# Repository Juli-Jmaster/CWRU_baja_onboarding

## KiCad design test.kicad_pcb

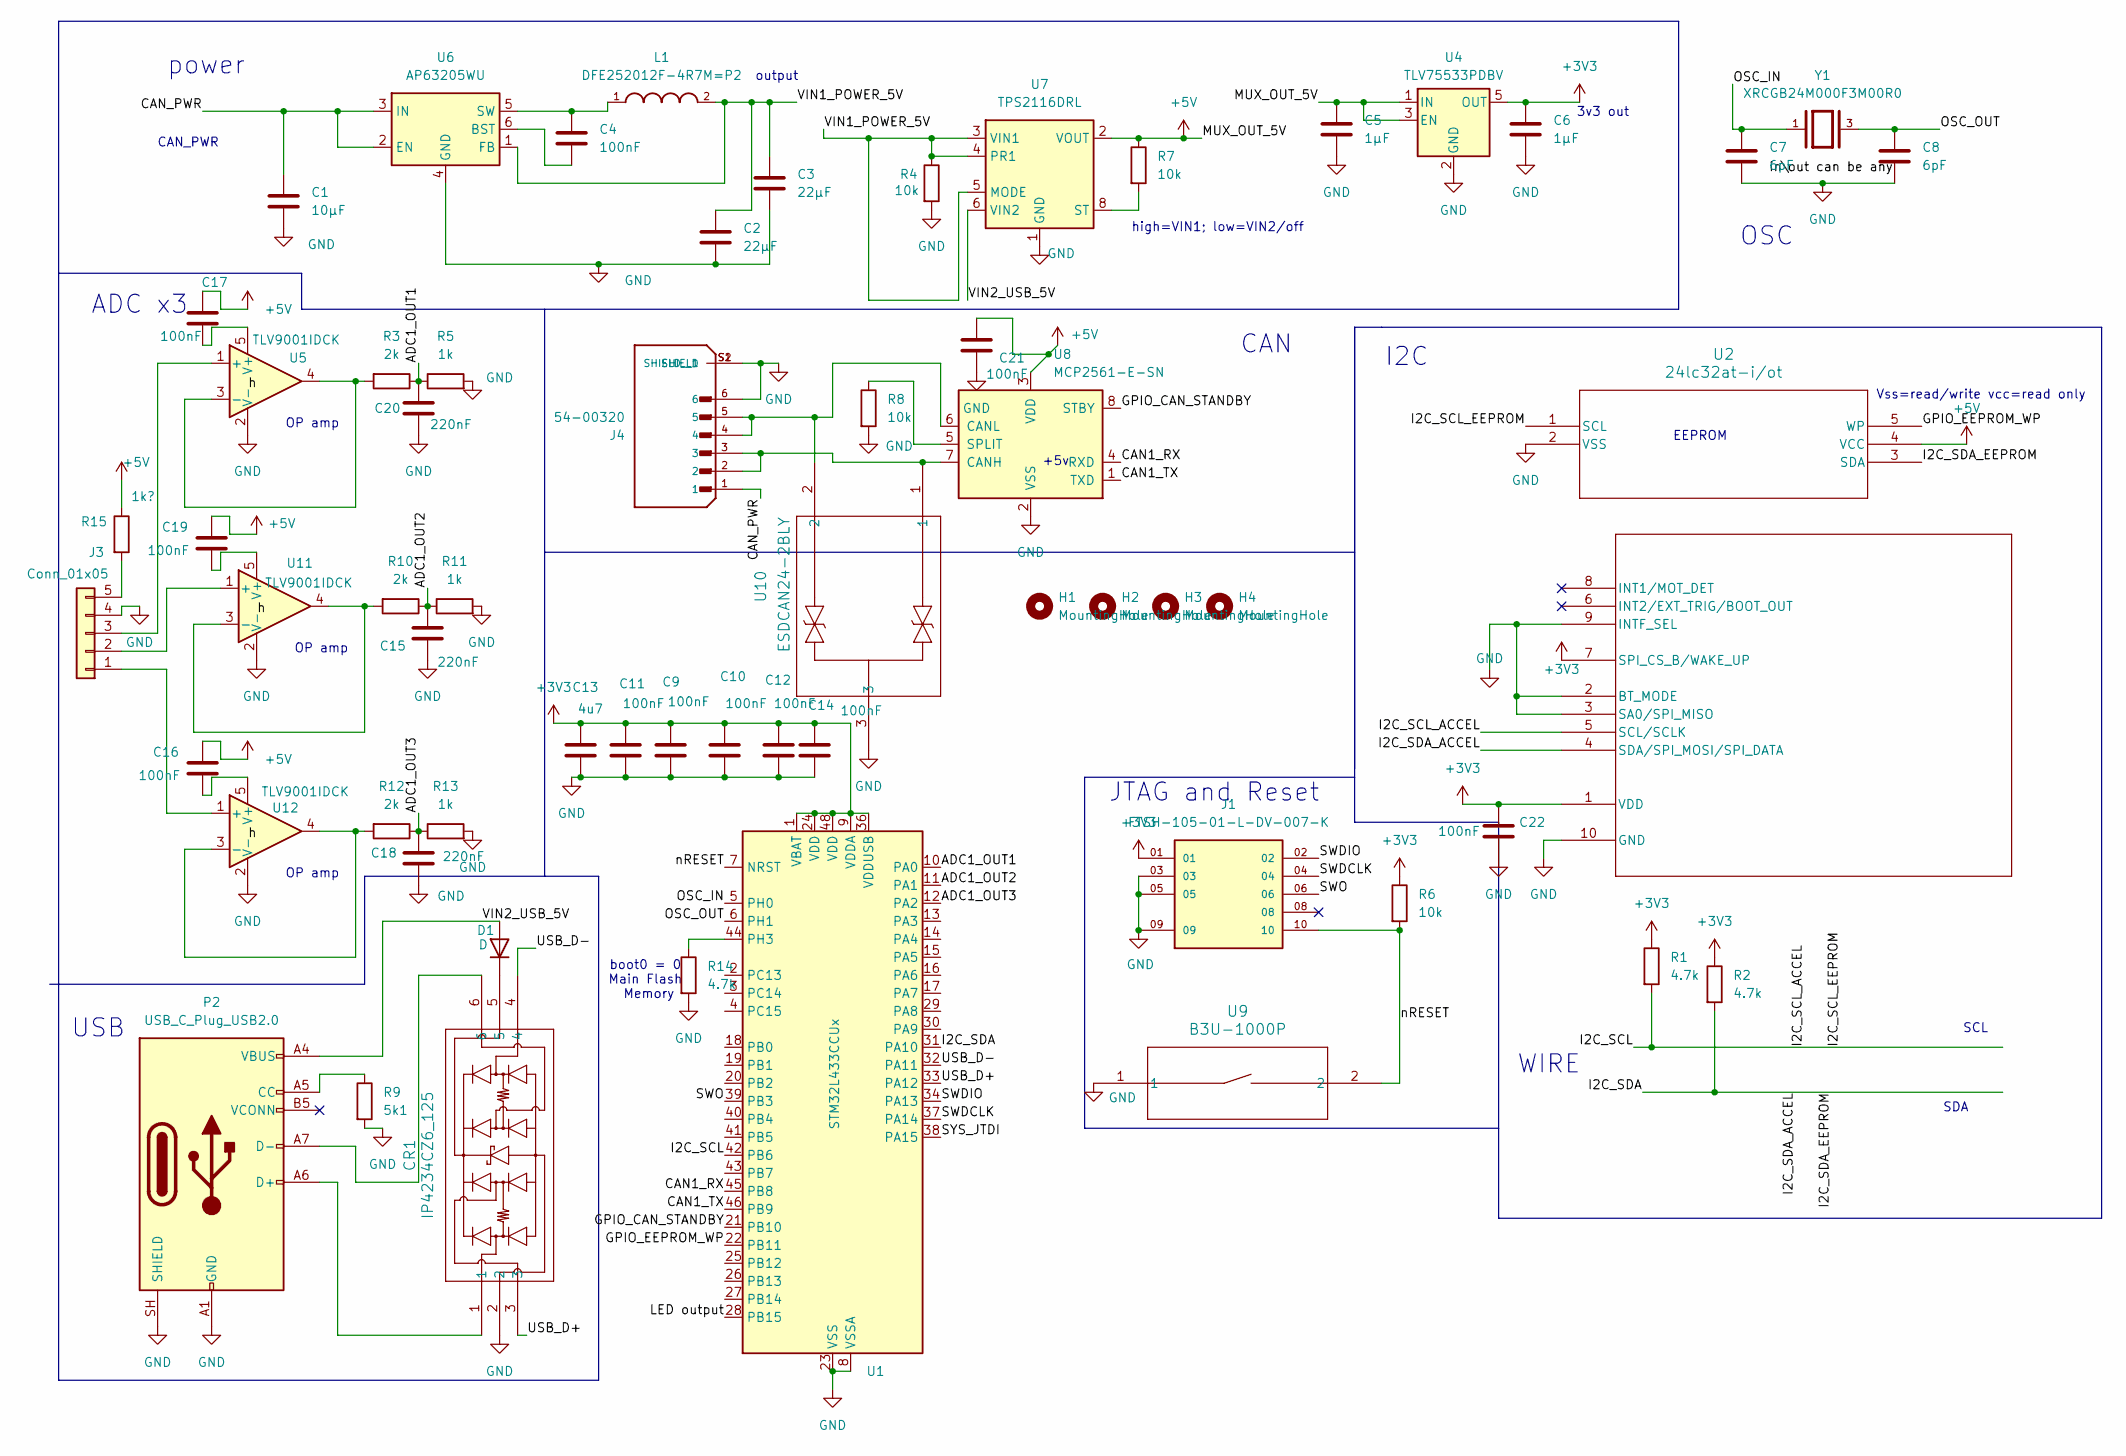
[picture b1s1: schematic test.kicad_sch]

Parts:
C1: 10μF; C_0603_1608Metric_Pad1.08x0.95mm_HandSolder
C2, C3: 22μF; C_0603_1608Metric_Pad1.08x0.95mm_HandSolder
C4, C9, C10, C11, C12, C14, C16, C17, C19, C21, C22: 100nF; C_0603_1608Metric_Pad1.08x0.95mm_HandSolder
C5, C6: 1μF; C_0603_1608Metric_Pad1.08x0.95mm_HandSolder
C7, C8: 6pF; C_0603_1608Metric_Pad1.08x0.95mm_HandSolder
C13: 4u7; C_0603_1608Metric_Pad1.08x0.95mm_HandSolder
C15, C18, C20: 220nF; C_0603_1608Metric_Pad1.08x0.95mm_HandSolder
CR1: IP4234CZ6_125; TSOP6_SOT457_NEX
D1: D; D_MELF
H1, H2, H3, H4: MountingHole; MountingHole_2.1mm
J1: FTSH-105-01-L-DV-007-K; SAMTEC_FTSH-105-01-L-DV-007-K; PARTREV H
J3: Conn_01x05; PinHeader_1x05_P2.54mm_Vertical
J4: 54-00320; TENSILITY_54-00320; PARTREV A
L1: DFE252012F-4R7M=P2; INDC2520X120N
P2: USB_C_Plug_USB2.0; USB_C_Receptacle_GCT_USB4085
R1, R2, R14: 4.7k; R_0603_1608Metric_Pad0.98x0.95mm_HandSolder
R3, R10, R12: 2k; R_0603_1608Metric_Pad0.98x0.95mm_HandSolder
R4, R6, R7, R8: 10k; R_0603_1608Metric_Pad0.98x0.95mm_HandSolder
R5, R11, R13: 1k; R_0603_1608Metric_Pad0.98x0.95mm_HandSolder
R9: 5k1; R_0603_1608Metric_Pad0.98x0.95mm_HandSolder
R15: 1k?; R_0603_1608Metric_Pad0.98x0.95mm_HandSolder
U1: STM32L433CCUx; QFN-48-1EP_7x7mm_P0.5mm_EP5.6x5.6mm
U2: 24lc32at-i/ot; SOT-24-5_MC_MCH
U3: FXLS8974CFR3; DFN10_2X2_STM
U4: TLV75533PDBV; SOT-23-5
U5, U11, U12: TLV9001IDCK; SOT-353_SC-70-5
U6: AP63205WU; TSOT-23-6
U7: TPS2116DRL; SOT-583-8
U8: MCP2561-E-SN; SOIC-8_3.9x4.9mm_P1.27mm
U9: B3U-1000P
U10: ESDCAN24-2BLY; SOT_24-2BLY_STM
Y1: XRCGB24M000F3M00R0; OSC_XRCGB24M000F3M00R0; PARTREV N/A

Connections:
+3V3: C6.1, C9.1, C10.1, C11.1, C12.1, C13.1, C14.1, C22.1, J1.01, R1.1, R2.1, R6.1, U1.1 (VBAT), U1.9 (VDDA), U1.24 (VDD), U1.36 (VDDUSB), U1.48 (VDD), U3.1 (VDD), U3.7 (SPI_CS_B/WAKE_UP), U4.5 (OUT)
+5V: C5.1, C16.2, C17.2, C19.2, C21.1, R7.1, R15.1, U2.4 (VCC), U4.1 (IN), U4.3 (EN), U7.2 (VOUT), U7.7 (VOUT), U8.3 (VDD)
/ADC1_OUT1: C20.1, R3.1, R5.1, U1.10 (PA0)
/ADC1_OUT2: C15.1, R10.1, R11.1, U1.11 (PA1)
/ADC1_OUT3: C18.1, R12.1, R13.1, U1.12 (PA2)
/CAN1_RX: U1.45 (PB8), U8.4 (RXD)
/CAN1_TX: U1.46 (PB9), U8.1 (TXD)
/CAN_PWR: C1.1, J4.1, U6.2 (EN), U6.3 (IN)
/GPIO_CAN_STANDBY: U1.21 (PB10), U8.8 (STBY)
/GPIO_EEPROM_WP: U1.22 (PB11), U2.5 (WP)
/I2C_SCL: R1.2, U1.42 (PB6), U2.1 (SCL), U3.5 (SCL/SCLK)
/I2C_SDA: R2.2, U1.31 (PA10), U2.3 (SDA), U3.4 (SDA/SPI_MOSI/SPI_DATA)
/LED output: U1.28 (PB15)
/OSC_IN: C7.1, U1.5 (PH0), Y1.1
/OSC_OUT: C8.1, U1.6 (PH1), Y1.3
/SWDCLK: J1.04, U1.37 (PA14)
/SWDIO: J1.02, U1.34 (PA13)
/SWO: J1.06, U1.39 (PB3)
/SYS_JTDI: U1.38 (PA15)
/USB_D+: CR1.3, U1.33 (PA12)
/USB_D-: CR1.4, U1.32 (PA11)
/VIN1_POWER_5V: C2.1, C3.1, L1.2, R4.1, U6.1 (FB), U7.3 (VIN1), U7.4 (PR1), U7.5 (MODE)
/VIN2_USB_5V: D1.2 (A), P2.A4 (VBUS), P2.A9 (VBUS), P2.B4 (VBUS), P2.B9 (VBUS), U7.6 (VIN2)
/nRESET: J1.10, R6.2, U1.7 (NRST), U9.2
GND: C1.2, C2.2, C3.2, C5.2, C6.2, C7.2, C8.2, C9.2, C10.2, C11.2, C12.2, C13.2, C14.2, C15.2, C18.2, C20.2, C21.2, C22.2, CR1.2, J1.03, J1.05, J1.09, J3.4, J4.6, J4.S1 (SHIELD), J4.S2 (SHIELD__1), P2.A1 (GND), P2.A12 (GND), P2.B1 (GND), P2.B12 (GND), P2.SH (SHIELD), R4.2, R5.2, R8.2, R9.2, R11.2, R13.2, R14.2, U1.8 (VSSA), U1.23 (VSS), U1.35 (VSS), U1.47 (VSS), U1.49 (VSS), U2.2 (VSS), U3.2 (BT_MODE), U3.3 (SA0/SPI_MISO), U3.9 (INTF_SEL), U3.10 (GND), U4.2 (GND), U5.2 (V-), U6.4 (GND), U7.1 (GND), U8.2 (VSS), U9.1, U10.3, U11.2 (V-), U12.2 (V-)
unnamed: CR1.5, D1.1 (K)
unnamed: J3.1, U12.1 (+)
unnamed: J3.2, U11.1 (+)
unnamed: J3.3, U5.1 (+)
unnamed: J3.5, R15.2
unnamed: P2.A5 (CC), R9.1
unnamed: CR1.1, P2.A6 (D+)
unnamed: CR1.6, P2.A7 (D-)
unnamed: R14.1, U1.44 (PH3)
unnamed: R3.2, U5.3 (-), U5.4
unnamed: C17.1, U5.5 (V+)
unnamed: C4.2, U6.6 (BST)
unnamed: C4.1, L1.1, U6.5 (SW)
unnamed: R7.2, U7.8 (ST)
unnamed: J4.2, J4.3, U8.7 (CANH), U10.1
unnamed: J4.4, J4.5, U8.6 (CANL), U10.2
unnamed: R8.1, U8.5 (SPLIT)
unnamed: R10.2, U11.3 (-), U11.4
unnamed: C19.1, U11.5 (V+)
unnamed: R12.2, U12.3 (-), U12.4
unnamed: C16.1, U12.5 (V+)

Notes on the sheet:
3v3 out
+5v
OP amp
WIRE
power
SDA
ADC x3
OSC
boot0 = 0 Main Flash Memory
Vss=read/write vcc=read only
JTAG and Reset
high=VIN1; low=VIN2/off
EEPROM
USB
output
CAN_PWR
SCL
I2C
CAN

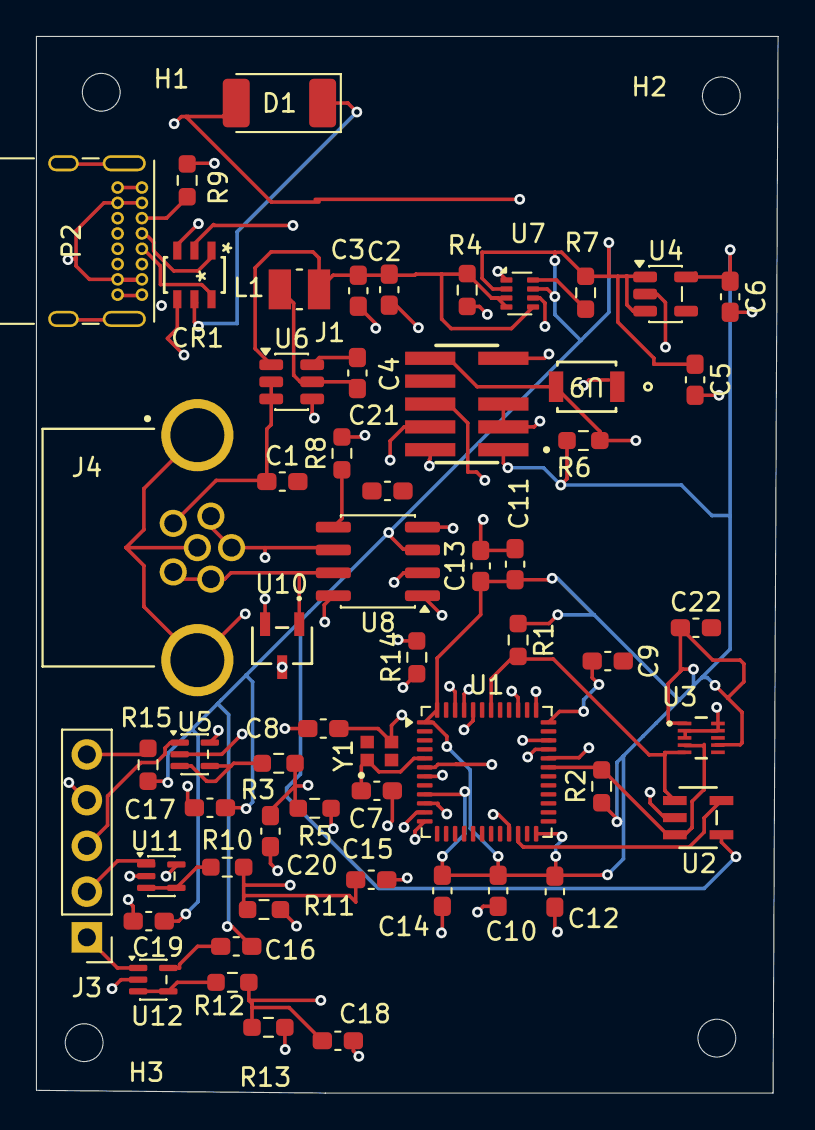
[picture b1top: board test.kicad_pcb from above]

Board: 4 copper layers, 41.2 x 58.7 mm, 61 parts (0 on the bottom side), 44 nets.

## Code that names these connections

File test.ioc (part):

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Mcu.Name=STM32L433C(B-C)Tx
Mcu.Package=LQFP48
Mcu.UserName=STM32L433CCTx
PA0.Signal=ADCx_IN5
PA1.Signal=ADCx_IN6
PA10.Mode=I2C
PA10.Signal=I2C1_SDA
PA11.GPIOParameters=GPIO_Label
PA11.GPIO_Label=USB_D-
PA11.Mode=Device
PA11.Signal=USB_DM
PA12.GPIOParameters=GPIO_Label
PA12.GPIO_Label=USB_D+
PA12.Mode=Device
PA12.Signal=USB_DP
PA13\ (JTMS-SWDIO).Mode=JTAG_4_pins
PA13\ (JTMS-SWDIO).Signal=SYS_JTMS-SWDIO
PA14\ (JTCK-SWCLK).Mode=JTAG_4_pins
PA14\ (JTCK-SWCLK).Signal=SYS_JTCK-SWCLK
PA15\ (JTDI).Mode=JTAG_4_pins
PA15\ (JTDI).Signal=SYS_JTDI
PA2.Signal=ADCx_IN7
PA8.GPIOParameters=GPIO_Label
PA8.GPIO_Label=GPIO OP amp in
PA8.Signal=GPIO_Input
PB10.GPIOParameters=GPIO_Label
PB10.GPIO_Label=GPIO_CAN_STANDBY
PB10.Signal=GPIO_Input
PB11.GPIOParameters=GPIO_Label
PB11.GPIO_Label=GPIO_EEPROM_WP
PB11.Signal=GPIO_Output
PB15.GPIOParameters=GPIO_Label
PB15.GPIO_Label=GPIO ouput LED
PB15.Signal=GPIO_Output
PB3\ (JTDO-TRACESWO).Mode=JTAG_4_pins
PB3\ (JTDO-TRACESWO).Signal=SYS_JTDO-SWO
PB6.Mode=I2C
PB6.Signal=I2C1_SCL
PB8.Mode=CAN_Activate
PB8.Signal=CAN1_RX
PB9.Mode=CAN_Activate
PB9.Signal=CAN1_TX
PH0-OSC_IN\ (PH0).Mode=HSE-External-Oscillator
PH0-OSC_IN\ (PH0).Signal=RCC_OSC_IN
PH1-OSC_OUT\ (PH1).Mode=HSE-External-Oscillator
PH1-OSC_OUT\ (PH1).Signal=RCC_OSC_OUT
RCC.HSE_VALUE=8000000
RCC.SYSCLKFreq_VALUE=80000000
RCC.SYSCLKSource=RCC_SYSCLKSOURCE_PLLCLK
board=custom
